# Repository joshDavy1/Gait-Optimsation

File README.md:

# Generation of Robot Gaits Using Low Level Parameters

Final Report

Joshua Davy

el17jd@leeds.ac.uk

May 2020

## Abstract

Traditionally the gaits of legged robots are inspired by what is seen in nature and
on assumptions of what properties the optimum gait would have. This involves
kinematic and dynamic analysis of the robot which becomes increasingly difficult
with robots with greater degrees of freedom. Further, real actuators and joints
are not ideal and are also difficult to mathematically model accurately. In this
project the aim is to use optimisation techniques to allow a robot to develop its
own gait free from human bias of what the optimum gait would look like. This
technique means no kinematic or dynamic analysis of a robot is necessary, as
the robot will attempt to learn a policy of moving its joints to optimise its gait.
The project will consist of two main sections, firstly the design and build of
a suitable robotic platform for experimentation and secondly, the investigation
and design of suitable software to control the robotic platform.

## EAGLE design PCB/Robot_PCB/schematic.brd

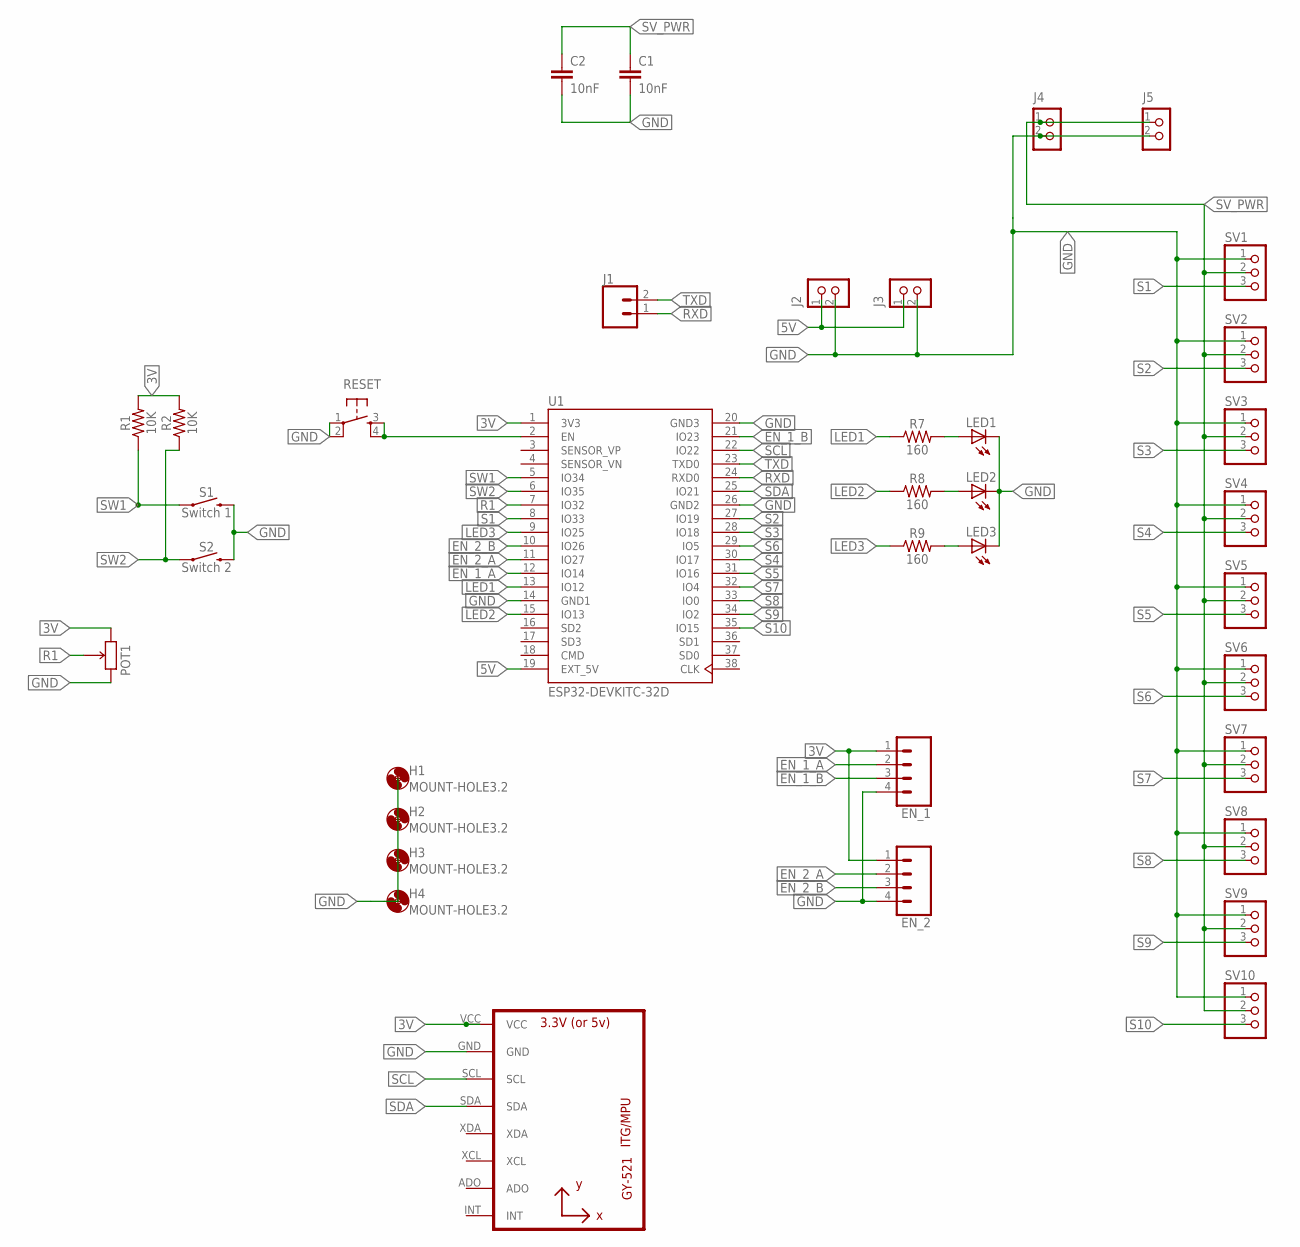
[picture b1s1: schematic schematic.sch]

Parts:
C1, C2: 10nF; CAP-PTH-10MM
EN_1, EN_2: CONN_04; 1X04
H1, H2, H3, H4: MOUNT-HOLE3.2; 3,2
J1: CONN_02; 1X02
J2, J3, J4, J5: CON_TERMINAL_BLOCK_02-5MM; TERMINAL_BLOCK_2P_5
LED1, LED2, LED3: LED3MM
POT1: POTENTIOMETER_THT; POTENTIOMETER
R1, R2: 10K; AXIAL-0.3
R7, R8, R9: 160; AXIAL-0.3
RESET: TAC_SWITCHPTH; TACTILE-PTH
S1: Switch 1; TACTILE_SWITCH_PTH_12MM
S2: Switch 2; TACTILE_SWITCH_PTH_12MM
SV1, SV2, SV3, SV4, SV5, SV6, SV7, SV8, SV9, SV10: PINHD-1X3; 1X03
U1: ESP32-DEVKITC-32D; MODULE_ESP32-DEVKITC-32D
U2: GY-521MPU6050; GY-521

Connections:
3V: EN_1.1, EN_2.1, POT1.3 (CW), R1.P$2 (2), R2.P$2 (2), U1.1 (3V3), U2.VCC
5V: J2.1, J3.1, U1.19 (EXT_5V)
EN_1_A: EN_1.2, U1.12 (IO14)
EN_1_B: EN_1.3, U1.21 (IO23)
EN_2_A: EN_2.2, U1.11 (IO27)
EN_2_B: EN_2.3, U1.10 (IO26)
GND: C1.2, C2.2, EN_1.4, EN_2.4, J2.2, J3.2, J4.2, J5.2, LED1.K (C), LED2.K (C), LED3.K (C), POT1.1 (CCW), RESET.1, RESET.2, S1.3 (2), S2.3 (2), SV1.1, SV2.1, SV3.1, SV4.1, SV5.1, SV6.1, SV7.1, SV8.1, SV9.1, SV10.1, U1.14 (GND1), U1.20 (GND3), U1.26 (GND2), U2.GND
LED1: R7.P$1 (1), U1.13 (IO12)
LED2: R8.P$1 (1), U1.15 (IO13)
LED3: R9.P$1 (1), U1.9 (IO25)
unnamed: RESET.3, RESET.4, U1.2 (EN)
unnamed: LED1.A, R7.P$2 (2)
unnamed: LED2.A, R8.P$2 (2)
unnamed: LED3.A, R9.P$2 (2)
R1: POT1.2 (WIPER), U1.7 (IO32)
RXD: J1.1, U1.24 (RXD0)
S1: SV1.3, U1.8 (IO33)
S2: SV2.3, U1.27 (IO19)
S3: SV3.3, U1.28 (IO18)
S4: SV4.3, U1.30 (IO17)
S5: SV5.3, U1.31 (IO16)
S6: SV6.3, U1.29 (IO5)
S7: SV7.3, U1.32 (IO4)
S8: SV8.3, U1.33 (IO0)
S9: SV9.3, U1.34 (IO2)
S10: SV10.3, U1.35 (IO15)
SCL: U1.22 (IO22), U2.SCL
SDA: U1.25 (IO21), U2.SDA
SV_PWR: C1.1, C2.1, J4.1, J5.1, SV1.2, SV2.2, SV3.2, SV4.2, SV5.2, SV6.2, SV7.2, SV8.2, SV9.2, SV10.2
SW1: R1.P$1 (1), S1.1, U1.5 (IO34)
SW2: R2.P$1 (1), S2.1, U1.6 (IO35)
TXD: J1.2, U1.23 (TXD0)

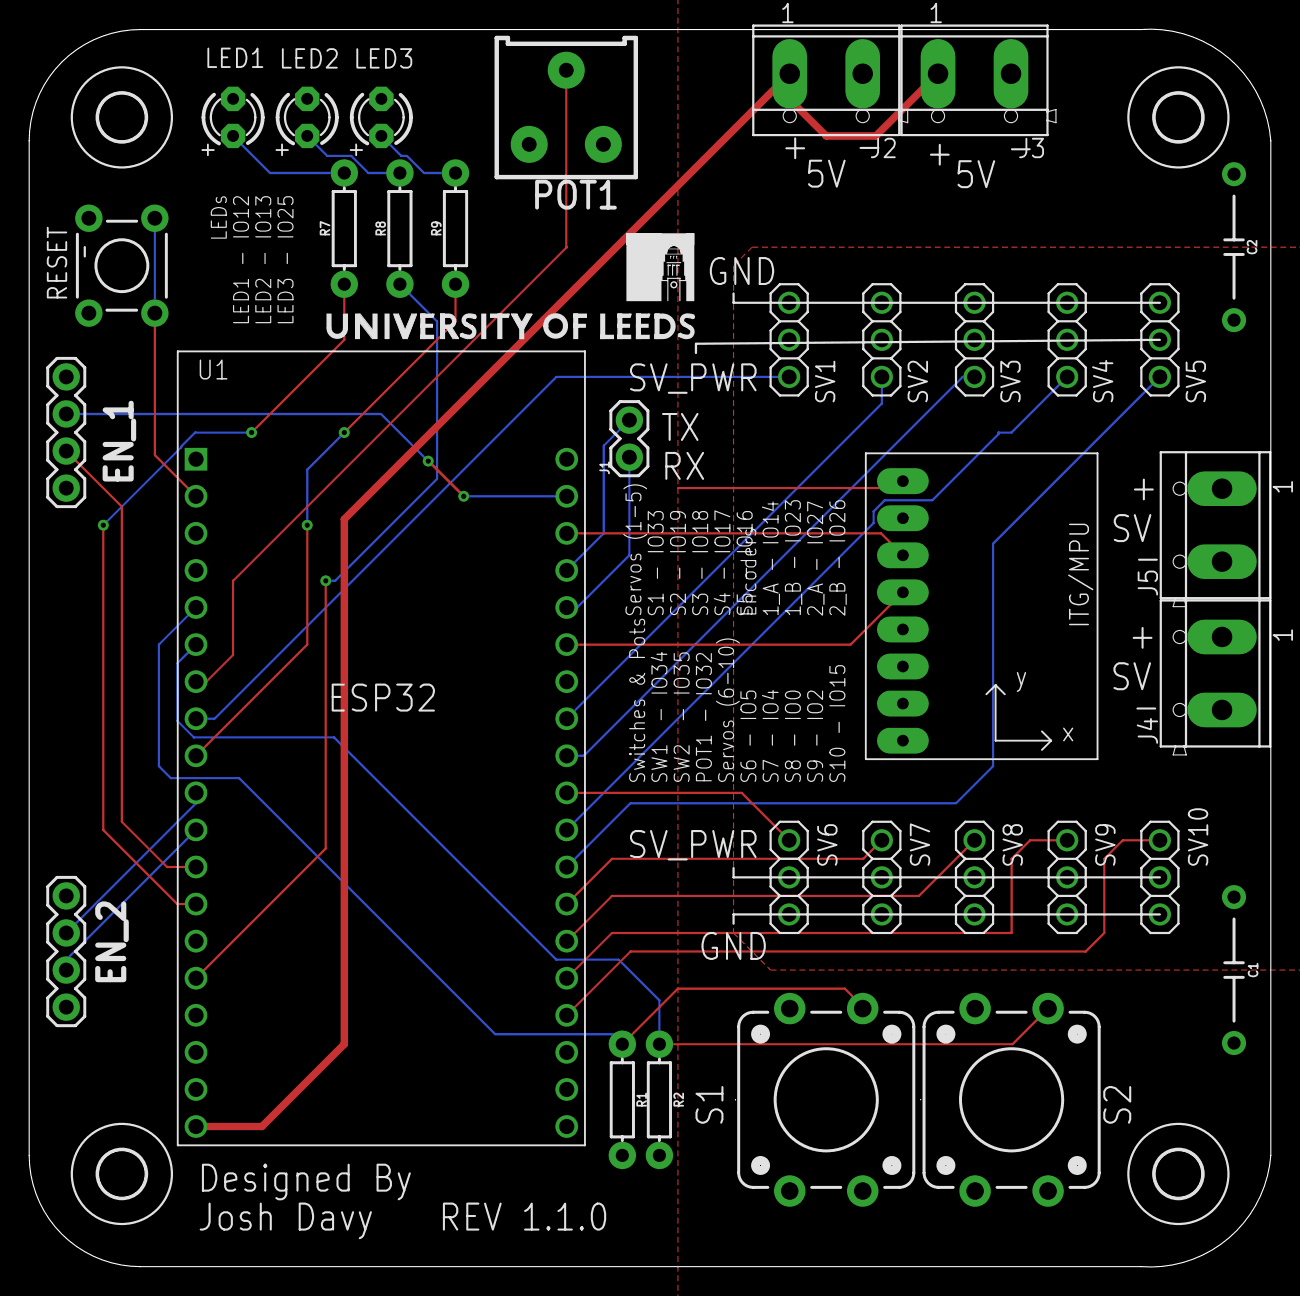
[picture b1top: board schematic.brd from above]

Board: 2 copper layers, 85.1 x 84.8 mm, 38 parts (0 on the bottom side), 32 nets.

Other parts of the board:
U$1: LOGO_LARGE

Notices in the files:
parts and their libraries:
SparkFun-Connectors: Licensing: Creative Commons ShareAlike 4.0 International - https://creativecommons.org/licenses/by-sa/4.0
